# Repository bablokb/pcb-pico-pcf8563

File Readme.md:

PCB Pico PCF8563
================

This is a simple breakout with the PCF8563 RTC. It will fit underneath the Pico. It uses
a solderless layout for the Pico-connectors and should hold by itself (but
this is highly dependent on e.g. your pins). As always, this is for prototyping,
you should solder the connectors for permanent projects and best results.

Hardware
--------

Ready to use production-files for JLCPCB are in the directory `production_files`.

Special use Jumpers
-------------------

There are three jumpers on the back for special use cases. You can cut the
trace between the jumper marked '3V3 VCC'. The RTC is then only powered by
one of the external connectors (pins or Stemma/Qt) and keeps on running
even if the Pico is shutdown.

The I2C pullups are hard-wired to 3V3, so even when powering the RTC
from an external source, you must still connect the 3V3-pin of the Pico
to the breakout.

If the external voltage is higher than 3V3 (e.g. from a LiPo), you should
also cut the traces labeled COUT and INT to protect the Pico.

License
-------

[![CC BY-SA 4.0][cc-by-sa-shield]][cc-by-sa]

This work is licensed under a
[Creative Commons Attribution-ShareAlike 4.0 International
License][cc-by-sa].

[![CC BY-SA 4.0][cc-by-sa-image]][cc-by-sa]

[cc-by-sa]: http://creativecommons.org/licenses/by-sa/4.0/
[cc-by-sa-image]: https://licensebuttons.net/l/by-sa/4.0/88x31.png
[cc-by-sa-shield]:
https://img.shields.io/badge/License-CC%20BY--SA%204.0-lightgrey.svg

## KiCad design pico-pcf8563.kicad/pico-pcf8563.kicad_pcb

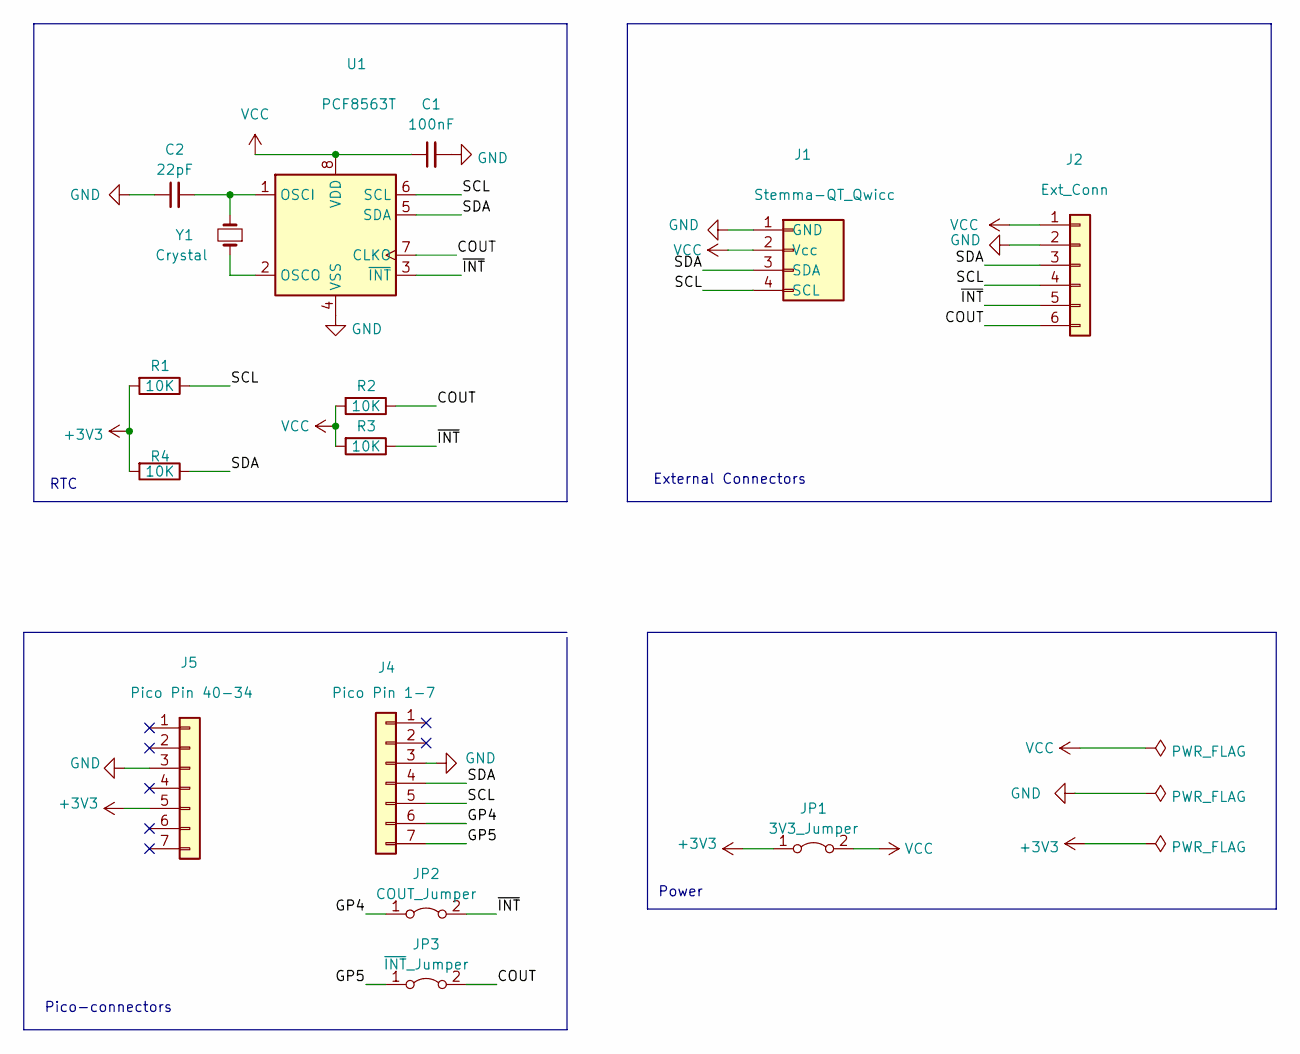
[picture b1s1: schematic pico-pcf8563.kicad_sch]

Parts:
C1: 100nF; C_0402_1005Metric; LCSC C1525
C2: 22pF; C_0402_1005Metric; LCSC C1555
J1: Stemma-QT_Qwicc; JST_SH_SM04B-SRSS-TB_1x04-1MP_P1.00mm_Horizontal
J2: Ext_Conn; PinHeader_1x06_P2.54mm_Vertical
J4: Pico Pin 1-7; Connector_1x7_no_solder
J5: Pico Pin 40-34; Connector_1x7_no_solder
JP1: 3V3_Jumper; SolderJumper-2_P1.3mm_Bridged_Pad1.0x1.5mm
JP2: COUT_Jumper; SolderJumper-2_P1.3mm_Bridged_Pad1.0x1.5mm
JP3: ~{INT}_Jumper; SolderJumper-2_P1.3mm_Bridged_Pad1.0x1.5mm
R1, R2, R3, R4: 10K; R_0402_1005Metric; LCSC C25744
U1: PCF8563T; SOIC-8_3.9x4.9mm_P1.27mm; LCSC C7440
Y1: Crystal; Crystal_SMD_3215-2Pin_3.2x1.5mm; LCSC C32346

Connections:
+3V3: J5.5, JP1.1 (A), R1.2, R4.2
/COUT: J2.6, JP3.2 (B), R2.1, U1.7 (CLKO)
/GP4: J4.6, JP2.1 (A)
/GP5: J4.7, JP3.1 (A)
/SCL: J1.4 (SCL), J2.4, J4.5, R1.1, U1.6 (SCL)
/SDA: J1.3 (SDA), J2.3, J4.4, R4.1, U1.5 (SDA)
/~INT: J2.5, JP2.2 (B), R3.1, U1.3 (~INT)
GND: C1.2, C2.1, J1.1 (GND), J2.2, J4.3, J5.3, U1.4 (VSS)
unnamed: C2.2, U1.1 (OSCI), Y1.2
unnamed: U1.2 (OSCO), Y1.1
VCC: C1.1, J1.2 (Vcc), J2.1, JP1.2 (B), R2.2, R3.2, U1.8 (VDD)

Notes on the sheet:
External Connectors
Power
Pico-connectors
RTC

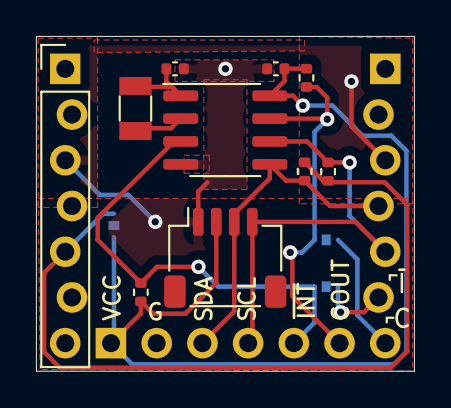
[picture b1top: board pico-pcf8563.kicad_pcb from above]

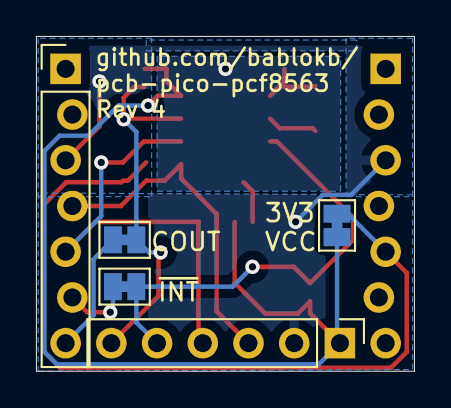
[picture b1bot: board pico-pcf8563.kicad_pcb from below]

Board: 2 copper layers, 21.0 x 18.6 mm, 15 parts (5 on the bottom side), 11 nets.

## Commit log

2023-01-26 Rev2
2023-01-27 removed backups
2023-01-27 Rev 3
2023-02-17 updated pcb from schematic for Rev3
2023-03-08 Rev 4: swapped INT/CLKOUT. The latter is now on GP5
2023-03-15 added section 'Hardware'
